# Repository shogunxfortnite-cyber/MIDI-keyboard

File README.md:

# MIDI-keyboard
A mini midi keyboard

## What i used
I used KICAD for making the overall schematic and pcb. 

For code we can either use a python script or c++(arduino ide) .

## How to make 
Check out https://github.com/KaiPereira/MIDI-Keypad/blob/master/README.md to see the step by step process.

You can either edit this or directly download it from my repo.

My repo has both the ino and py script.

## BOM

| Part | Qty | Unit | Total | Vendor | Link |
| :--- | :--- | :--- | :--- | :--- | :--- |
| Kailh Choc Low-Profile Switches (The switches) | 1 | $7.00 | $7.00 | Neo Macro | https://neomacro.in/products/kailh-choc-v2-low-profile-switches?variant=51316563312918 |
| ESP32-S3-Zero (The main board) | 1 | $6.00 | $6.00 | Robocraze | https://robocraze.com/products/waveshare-esp32-s3-zero-development-board-240mhz?variant=54460076327136 |
| EC11 (The rotary encoder) | 1 | $3.00 | $3.00 | Amazon | https://www.amazon.in/gp/product/B0DCC932SC/ref=ewc_pr_img_2?smid=A394MJGYEIL46Y&psc=1 |
| The LED (The light function) | 1 | $4.00 | $4.00 | Amazon | https://www.amazon.in/gp/product/B0HFX8SBG8/ref=ewc_pr_img_2?smid=A2UYDSF8DPIGX4&th=1 |
| Potentiometer_Bourns_PTA1543_Single_Slide (The sliding part) | 2 | $2.00 | $4.00 | Element 14 India | https://in.element14.com/bourns/pta3043-2010cib103/pot-slide-10kohm-0-2w/dp/2519655 |
| The PCB (Holding all the components) | 1 | $6.00 | $6.00 | Robu | robu.in |
| **Total** | | | **$30.00** | | |

## Schematic

## PCB

## KICAD symbols and footprints 

You can find these at https://github.com/KaiPereira/MIDI-Keypad

## made for hack club 
This project is made for hack club

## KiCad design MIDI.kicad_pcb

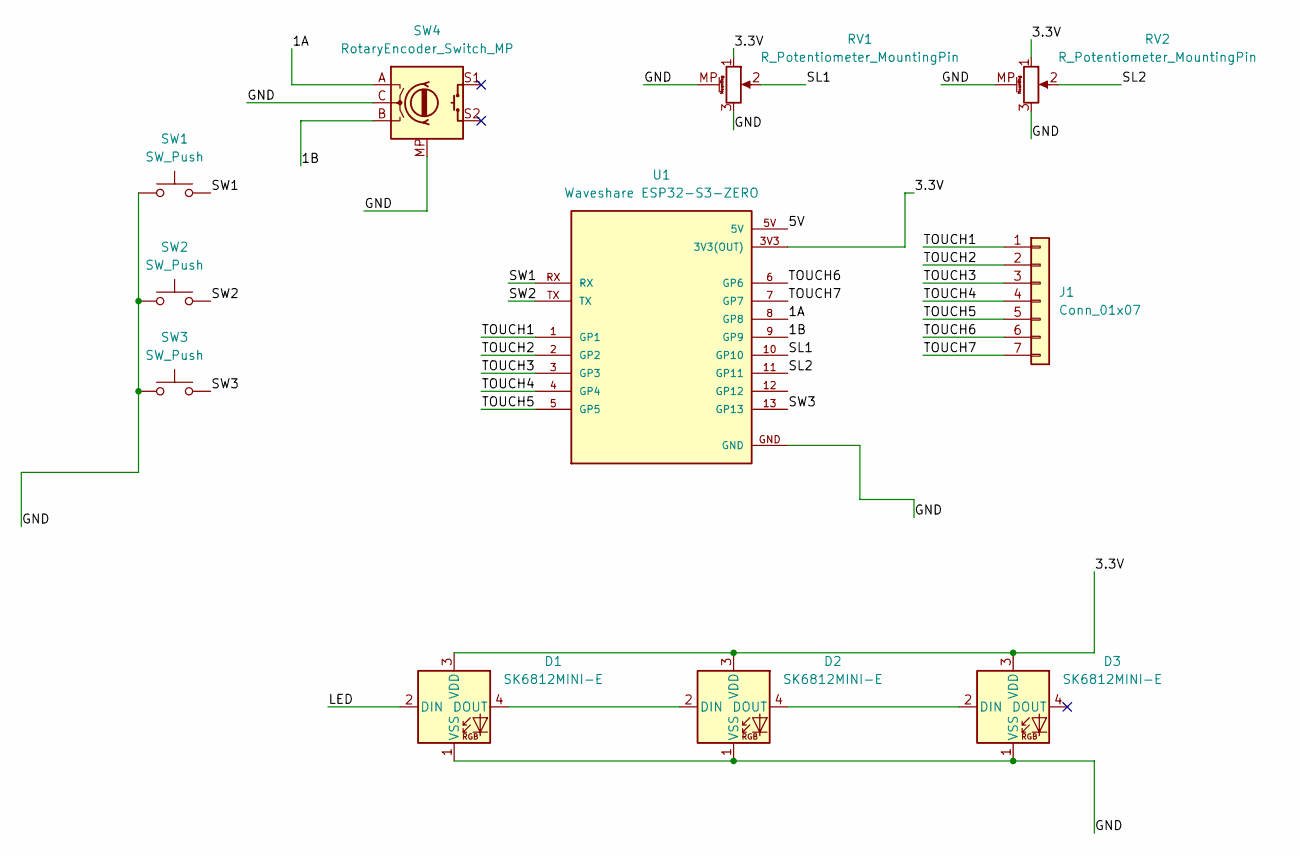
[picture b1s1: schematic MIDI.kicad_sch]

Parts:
D1, D2, D3: SK6812MINI-E; LED_SK6812MINI-E_3.2x2.8mm_P1.5mm_ReverseMount
J1: Conn_01x07; circle 2
RV1, RV2: R_Potentiometer_MountingPin; Potentiometer_Bourns_PTA1543_Single_Slide
SW1, SW2, SW3: SW_Push; Kailh Choc Low-Profile Switches
SW4: RotaryEncoder_Switch_MP; RotaryEncoder_Alps_EC11E-Switch_Vertical_H20mm
U1: Waveshare ESP32-S3-ZERO; Waveshare ESP32-S3-Zero; PARTREV NA

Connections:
/1A: SW4.A, U1.8 (GP8)
/1B: SW4.B, U1.9 (GP9)
/3.3V: D1.3 (VDD), D2.3 (VDD), D3.3 (VDD), RV1.1, RV2.1, U1.3V3 (3V3(OUT))
/5V: U1.5V
/GND: D1.1 (VSS), D2.1 (VSS), D3.1 (VSS), RV1.3, RV1.MP (MountPin), RV2.3, RV2.MP (MountPin), SW1.1, SW2.1, SW3.1, SW4.C, SW4.MP, U1.GND
/LED: D1.2 (DIN)
/SL1: RV1.2, U1.10 (GP10)
/SL2: RV2.2, U1.11 (GP11)
/SW1: SW1.2, U1.RX
/SW2: SW2.2, U1.TX
/SW3: SW3.2, U1.13 (GP13)
/TOUCH1: J1.1, U1.1 (GP1)
/TOUCH2: J1.2, U1.2 (GP2)
/TOUCH3: J1.3, U1.3 (GP3)
/TOUCH4: J1.4, U1.4 (GP4)
/TOUCH5: J1.5, U1.5 (GP5)
/TOUCH6: J1.6, U1.6 (GP6)
/TOUCH7: J1.7, U1.7 (GP7)
unnamed: D1.4 (DOUT), D2.2 (DIN)
unnamed: D2.4 (DOUT), D3.2 (DIN)

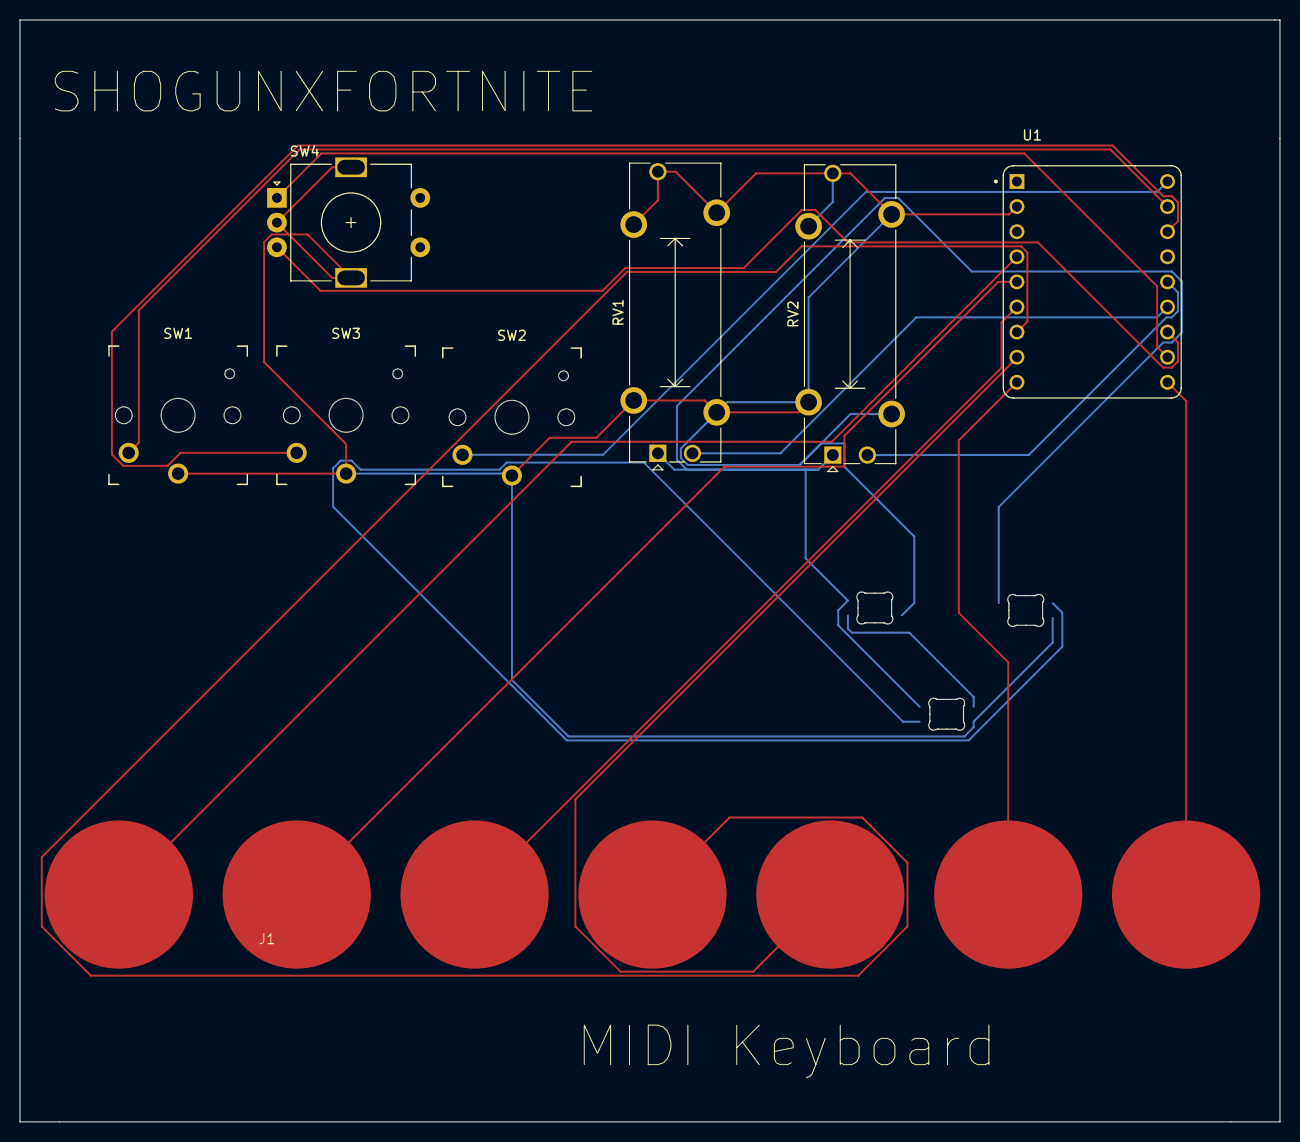
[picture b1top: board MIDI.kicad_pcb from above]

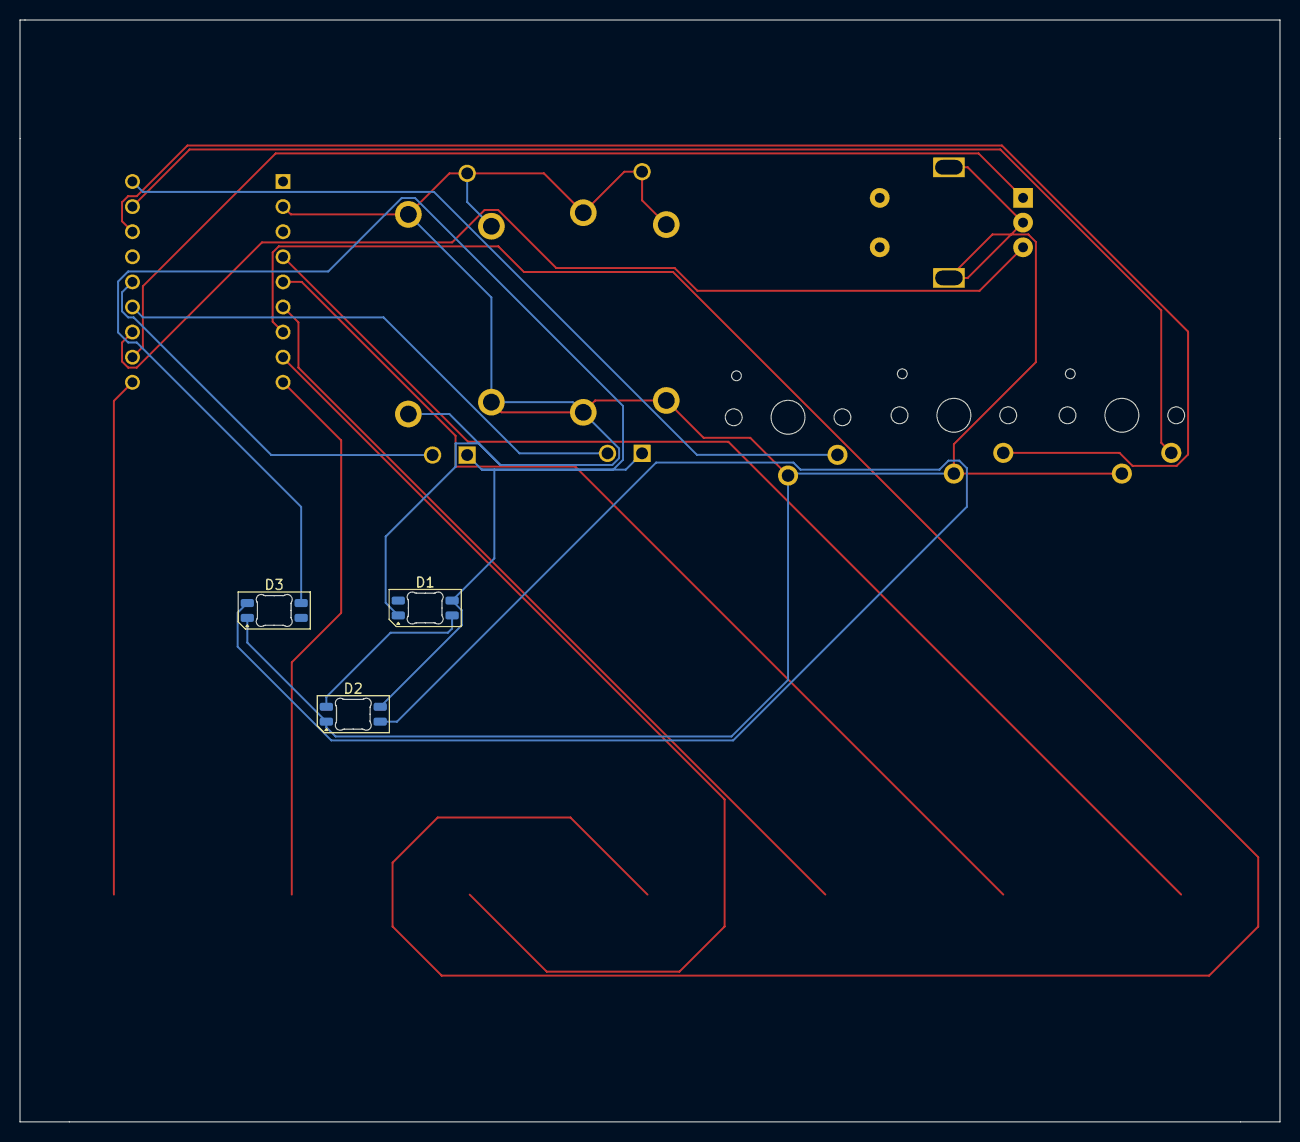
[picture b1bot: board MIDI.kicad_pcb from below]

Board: 2 copper layers, 127.5 x 111.5 mm, 11 parts (3 on the bottom side), 18 nets.
